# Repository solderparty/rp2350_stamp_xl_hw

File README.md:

# The RP2350 Stamp XL

The Stamp was created to allow you to use the **Raspberry Pi RP2350B** in your designs without having to solder small-pitch QFN chips or worry about lots of external circuitry.

The RP2350 Stamp XL is partially pad-compatible with the smaller Stamps. The left-side pads as well as half of the top and bottom ones are exactly the same.

All you need to get you started is a 5V supply or a LiPo battery. The Stamp will take care of the charging and switching the power sources.

The castellated edges with **2mm pitch** can be hand-soldered directly to a Carrier board, used with pin headers for more flexibility, or connected without soldering using [FlexyPins](https://docs.solder.party/flexypin), which are spring connectors designed for modules with castellated edges. You can find footprints for many PCB programs [here](https://github.com/solderparty/rp2xxx_stamp_footprints).

We were also able to squeeze in two new functional pads: an LDO EN pad, connected to the LDOs EN signal, and a BAT STAT, connected to the LiPo charger's STAT pin.

At only **1 by 1¾ inch**, the Stamp XL packs a lot of features:
* **16MB of FLASH**
* **500mA 3.3V LDO**
* **All 48 GPIOs broken out**
* **A footprint for a second QSPI FLASH/PSRAM**
* Footprints for SWD and UART JST connectors, pin-compatible with the Raspberry Pi Debug Probe
* LiPo supply and charging circuit (with charging LED)
* USB broken out
* SWD broken out
* Reset Button
* Bootsel Button
* 12MHz crystal

and of course, everything that comes with the Raspberry Pi RP2350 itself:
* Dual core ARM Cortex-M33 or Hazard3 @ 150MHz
* 520kB SRAM
* 2 UARTs
* 2 SPIs
* 2 I2Cs
* 24 PWM channels
* 12 PIO state machines
* 1 HSTX peripheral
* USB with Host and Device support

The RP2350 comes with a pre-programmed ROM UF2 Bootloader, by pulling the BOOTSEL pin low and resetting, or by double-pressing the RESET button (if the FW supports it), you can upload new firmware using the USB disk drive.

In addition to the Stamps we also offer a few reference designs, see the Carriers in the [Stamp-related category](https://docs.solder.party/rp2xxx-stamp-related) as well as our [Flux projects](https://docs.solder.party/flux).

The CircuitPython firmware for the Stamp comes with a built-in board files for the Carriers, for example you can access the RP2040 Stamp Carrier pins and interfaces by using `import stamp_carrier_board as board`. See [here](https://github.com/adafruit/circuitpython/tree/main/ports/raspberrypi/boards/solderparty_rp2040_stamp) for all the available Carrier board files.

# Links

For more information visit https://rp2350-stamp-xl.solder.party/

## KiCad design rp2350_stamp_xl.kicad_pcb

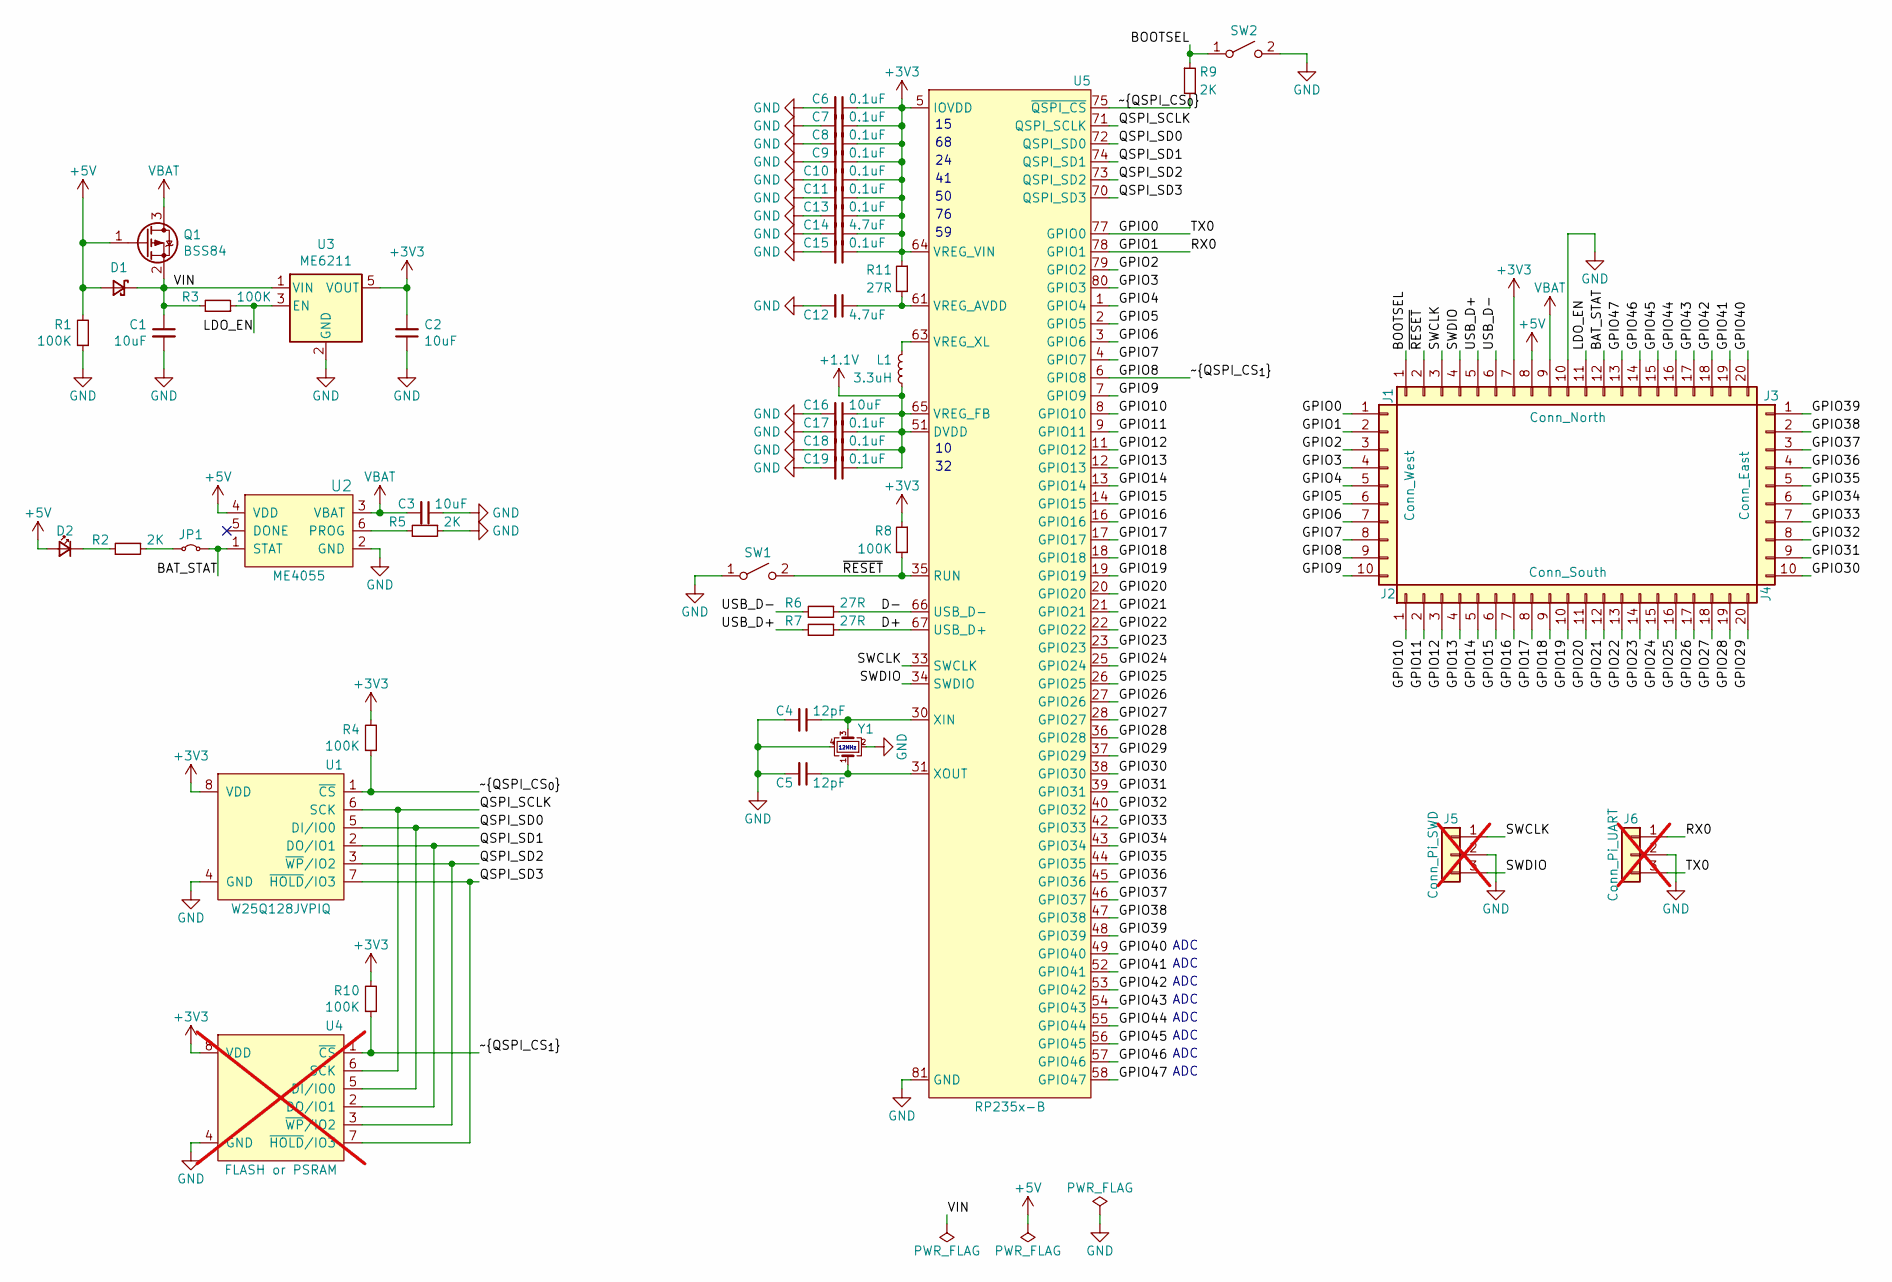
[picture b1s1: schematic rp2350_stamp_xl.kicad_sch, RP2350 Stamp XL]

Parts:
C1, C2, C3, C16: 10uF; C_0603_1608Metric
C4, C5: 12pF; C_0603_1608Metric
C6, C7, C8, C9, C10, C11, C13, C15, C17, C18, C19: 0.1uF; C_0603_1608Metric
C12, C14: 4.7uF; C_0603_1608Metric
D1: D_Schottky_Small; D_SOD-323; LCSC C114023
D2: LED_CHR; LED_0603_1608Metric
J1: Conn_North; Castellated_1x20_P2.00mm_Vertical
J2: Conn_West; Castellated_1x10_P2.00mm_Vertical
J3: Conn_East; Castellated_1x10_P2.00mm_Vertical
J4: Conn_South; Castellated_1x20_P2.00mm_Vertical
J5: Conn_Pi_SWD; JST_SH_BM03B-SRSS-TB_1x03-1MP_P1.00mm_Vertical; LCSC C7433439; not fitted
J6: Conn_Pi_UART; JST_SH_BM03B-SRSS-TB_1x03-1MP_P1.00mm_Vertical; LCSC C7433439; not fitted
JP1: SJ_STAT_LED; SolderJumper-2_P1.3mm_Bridged_RoundedPad1.0x1.5mm
L1: 3.3uH; L_Wuerth_MAPI-2512; LCSC C5832359
Q1: BSS84; SOT-23; LCSC C85202
R1, R3, R4, R8, R10: 100K; R_0603_1608Metric
R2, R5, R9: 2K; R_0603_1608Metric
R6, R7, R11: 27R; R_0603_1608Metric
SW1: SW_RESET; SW_SPST_B3U-1000P; LCSC C561514
SW2: SW_BOOTSEL; SW_SPST_B3U-1000P; LCSC C561514
U1: W25Q128JVPIQ; WSON-8-1EP_6x5mm_P1.27mm_EP3.4x4mm; LCSC C190862
U2: ME4055; SOT-23-6; LCSC C82121
U3: ME6211; SOT-23-5; LCSC C82942
U4: FLASH or PSRAM; SSOP-8_5.25x5.24mm_P1.27mm; not fitted
U5: RP235x-B; QFN-80_EP_10x10_Pitch0.4mm
Y1: CM4012M00012001; Crystal_SMD_2520-4Pin_2.5x2.0mm; LCSC C7294611

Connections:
+1.1V: C16.1, C17.1, C18.1, C19.1, L1.1, U5.10 (DVDD), U5.32 (DVDD), U5.51 (DVDD), U5.65 (VREG_FB)
+3V3: C2.2, C6.1, C7.1, C8.1, C9.1, C10.1, C11.1, C13.1, C14.1, C15.1, J1.7, R4.2, R8.1, R10.2, R11.1, U1.8 (VDD), U3.5 (VOUT), U4.8 (VDD), U5.5 (IOVDD), U5.15 (IOVDD), U5.24 (IOVDD), U5.29 (IOVDD), U5.41 (IOVDD), U5.50 (IOVDD), U5.59 (IOVDD), U5.60 (IOVDD), U5.64 (VREG_VIN), U5.68 (IOVDD), U5.69 (IOVDD), U5.76 (IOVDD)
+5V: D1.2 (A), D2.2 (A), J1.8, Q1.1 (G), R1.2, U2.4 (VDD)
/BAT_STAT: J1.12, JP1.2 (B), U2.1 (STAT)
/BOOTSEL: J1.1, R9.1, SW2.1 (A)
/D+: R7.1, U5.67 (USB_D+)
/D-: R6.1, U5.66 (USB_D-)
/GPIO0: J2.1, J6.3, U5.77 (GPIO0)
/GPIO1: J2.2, J6.1, U5.78 (GPIO1)
/GPIO2: J2.3, U5.79 (GPIO2)
/GPIO3: J2.4, U5.80 (GPIO3)
/GPIO4: J2.5, U5.1 (GPIO4)
/GPIO5: J2.6, U5.2 (GPIO5)
/GPIO6: J2.7, U5.3 (GPIO6)
/GPIO7: J2.8, U5.4 (GPIO7)
/GPIO8: J2.9, R10.1, U4.1 (~CS), U5.6 (GPIO8)
/GPIO9: J2.10, U5.7 (GPIO9)
/GPIO10: J4.1, U5.8 (GPIO10)
/GPIO11: J4.2, U5.9 (GPIO11)
/GPIO12: J4.3, U5.11 (GPIO12)
/GPIO13: J4.4, U5.12 (GPIO13)
/GPIO14: J4.5, U5.13 (GPIO14)
/GPIO15: J4.6, U5.14 (GPIO15)
/GPIO16: J4.7, U5.16 (GPIO16)
/GPIO17: J4.8, U5.17 (GPIO17)
/GPIO18: J4.9, U5.18 (GPIO18)
/GPIO19: J4.10, U5.19 (GPIO19)
/GPIO20: J4.11, U5.20 (GPIO20)
/GPIO21: J4.12, U5.21 (GPIO21)
/GPIO22: J4.13, U5.22 (GPIO22)
/GPIO23: J4.14, U5.23 (GPIO23)
/GPIO24: J4.15, U5.25 (GPIO24)
/GPIO25: J4.16, U5.26 (GPIO25)
/GPIO26: J4.17, U5.27 (GPIO26)
/GPIO27: J4.18, U5.28 (GPIO27)
/GPIO28: J4.19, U5.36 (GPIO28)
/GPIO29: J4.20, U5.37 (GPIO29)
/GPIO30: J3.10, U5.38 (GPIO30)
/GPIO31: J3.9, U5.39 (GPIO31)
/GPIO32: J3.8, U5.40 (GPIO32)
/GPIO33: J3.7, U5.42 (GPIO33)
/GPIO34: J3.6, U5.43 (GPIO34)
/GPIO35: J3.5, U5.44 (GPIO35)
/GPIO36: J3.4, U5.45 (GPIO36)
/GPIO37: J3.3, U5.46 (GPIO37)
/GPIO38: J3.2, U5.47 (GPIO38)
/GPIO39: J3.1, U5.48 (GPIO39)
/GPIO40: J1.20, U5.49 (GPIO40)
/GPIO41: J1.19, U5.52 (GPIO41)
/GPIO42: J1.18, U5.53 (GPIO42)
/GPIO43: J1.17, U5.54 (GPIO43)
/GPIO44: J1.16, U5.55 (GPIO44)
/GPIO45: J1.15, U5.56 (GPIO45)
/GPIO46: J1.14, U5.57 (GPIO46)
/GPIO47: J1.13, U5.58 (GPIO47)
/LDO_EN: J1.11, R3.1, U3.3 (EN)
/QSPI_SCLK: U1.6 (SCK), U4.6 (SCK), U5.71 (QSPI_SCLK)
/QSPI_SD0: U1.5 (DI/IO0), U4.5 (DI/IO0), U5.72 (QSPI_SD0)
/QSPI_SD1: U1.2 (DO/IO1), U4.2 (DO/IO1), U5.74 (QSPI_SD1)
/QSPI_SD2: U1.3 (~WP/IO2), U4.3 (~WP/IO2), U5.73 (QSPI_SD2)
/QSPI_SD3: U1.7 (~HOLD/IO3), U4.7 (~HOLD/IO3), U5.70 (QSPI_SD3)
/SWCLK: J1.3, J5.1, U5.33 (SWCLK)
/SWDIO: J1.4, J5.3, U5.34 (SWDIO)
/USB_D+: J1.5, R7.2
/USB_D-: J1.6, R6.2
/VIN: C1.1, D1.1 (K), Q1.2 (S), R3.2, U3.1 (VIN)
/~QSPI_CS_{0}: R4.1, R9.2, U1.1 (~CS), U5.75 (~QSPI_CS)
/~RESET: J1.2, R8.2, SW1.2 (B), U5.35 (RUN)
GND: C1.2, C2.1, C3.1, C4.2, C5.2, C6.2, C7.2, C8.2, C9.2, C10.2, C11.2, C12.2, C13.2, C14.2, C15.2, C16.2, C17.2, C18.2, C19.2, J1.10, J5.2, J6.2, R1.1, R5.1, SW1.1 (A), SW2.2 (B), U1.4 (GND), U1.9 (GND), U2.2 (GND), U3.2 (GND), U4.4 (GND), U4.9 (GND), U5.62 (GND), U5.81 (GND), Y1.2, Y1.4
unnamed: D2.1 (K), R2.2
unnamed: JP1.1 (A), R2.1
unnamed: R5.2, U2.6 (PROG)
unnamed: C12.1, R11.2, U5.61 (VREG_AVDD)
unnamed: L1.2, U5.63 (VREG_XL)
unnamed: C4.1, U5.30 (XIN), Y1.3
unnamed: C5.1, U5.31 (XOUT), Y1.1
VBAT: C3.2, J1.9, Q1.3 (D), U2.3 (VBAT)

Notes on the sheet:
ADC
12MHz

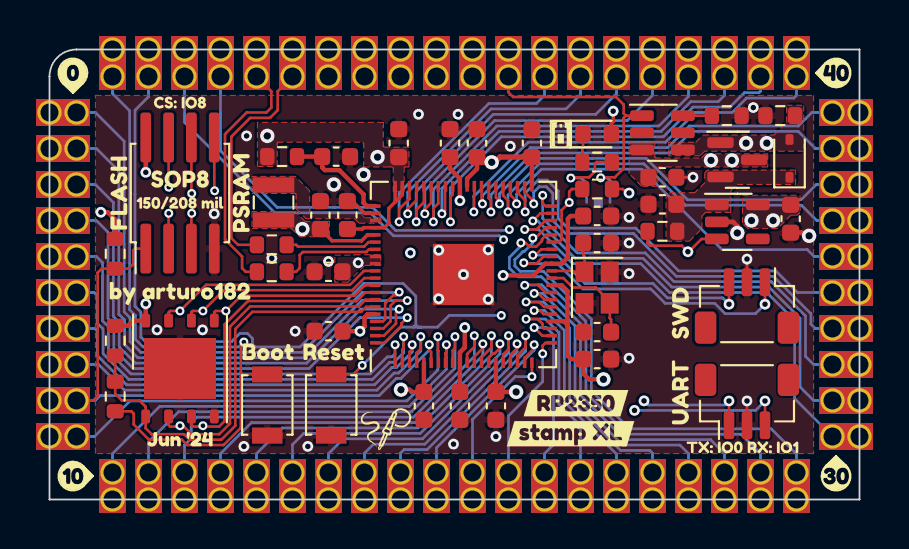
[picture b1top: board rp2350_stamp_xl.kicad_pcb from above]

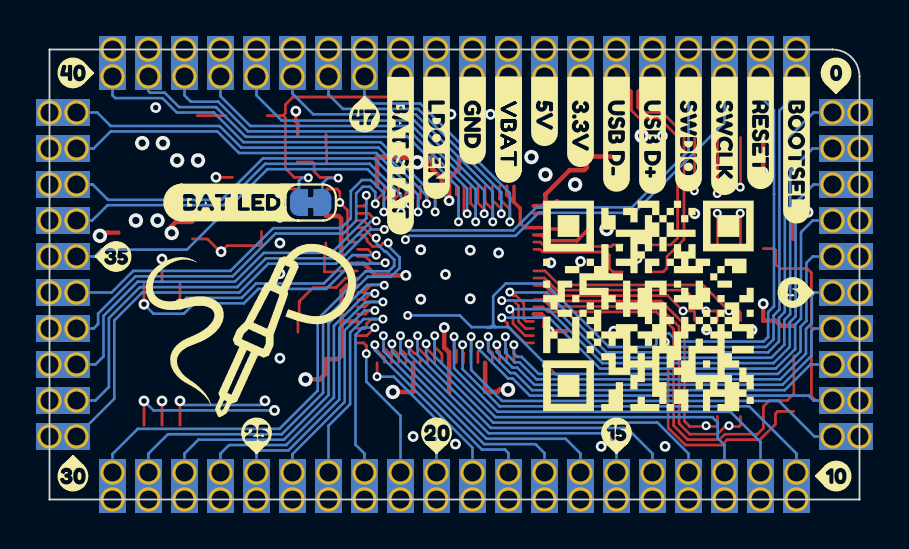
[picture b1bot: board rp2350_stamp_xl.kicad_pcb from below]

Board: 4 copper layers, 45.0 x 25.0 mm, 93 parts (26 on the bottom side), 77 nets.

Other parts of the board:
SP-LOGO: LOGO; SolderParty-New-Logo_3x2.5mm_SilkScreen
kibuzzard-65C6A7E6: G***; kibuzzard-65C6A7E6
kibuzzard-65C6A7EF: G***; kibuzzard-65C6A7EF
kibuzzard-65C6A855: G***; kibuzzard-65C6A855
kibuzzard-65C6A858: G***; kibuzzard-65C6A858
kibuzzard-65C59B9B: G***; kibuzzard-65C59B9B
kibuzzard-65C557A7: G***; kibuzzard-65C557A7
kibuzzard-65C55791: G***; kibuzzard-65C55791
kibuzzard-65CABD6A: G***; kibuzzard-65CABD6A
kibuzzard-65CABE96: G***; kibuzzard-65CABE96
kibuzzard-65CABECC: G***; kibuzzard-65CABECC
kibuzzard-653BD2BD: G***; kibuzzard-653BD2BD
kibuzzard-653BD2D7: G***; kibuzzard-653BD2D7
kibuzzard-653BD2FF: G***; kibuzzard-653BD2FF
kibuzzard-653BD3DA: G***; kibuzzard-653BD3DA
kibuzzard-653BD34E: G***; kibuzzard-653BD34E
kibuzzard-653BD35B: G***; kibuzzard-653BD35B
kibuzzard-653BD327: G***; kibuzzard-653BD327
kibuzzard-653BD339: G***; kibuzzard-653BD339
kibuzzard-653BD344: G***; kibuzzard-653BD344
kibuzzard-653BD355: G***; kibuzzard-653BD355
kibuzzard-653BD365: G***; kibuzzard-653BD365
kibuzzard-6577C6A3: G***; kibuzzard-6577C6A3
kibuzzard-6577C69C: G***; kibuzzard-6577C69C
kibuzzard-6578FE34: G***; kibuzzard-6578FE34
kibuzzard-6605B0A1: G***; kibuzzard-6605B0A1
kibuzzard-6605B0D5: G***; kibuzzard-6605B0D5
kibuzzard-6695ACF2, kibuzzard-6695ACF2#2: G***; kibuzzard-6695ACF2
kibuzzard-6695AD18, kibuzzard-6695AD18#2: G***; kibuzzard-6695AD18
kibuzzard-6695BC9C: G***; kibuzzard-6695BC9C
kibuzzard-6695BCB6: G***; kibuzzard-6695BCB6
kibuzzard-6695BF60, kibuzzard-6695BF60#2: G***; kibuzzard-6695BF60
kibuzzard-6695BFEA, kibuzzard-6695BFEA#2: G***; kibuzzard-6695BFEA
kibuzzard-6695C3C8: G***; kibuzzard-6695C3C8
kibuzzard-6695C4C9: G***; kibuzzard-6695C4C9
kibuzzard-6695C24F: G***; kibuzzard-6695C24F
kibuzzard-6695C28C: G***; kibuzzard-6695C28C
kibuzzard-6695C219: G***; kibuzzard-6695C219
kibuzzard-6695C372: G***; kibuzzard-6695C372
svg2mod: G***; svg2mod

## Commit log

2024-02-13 Rev 1
2024-07-16 Rev 3
    - Rev 2 added logo and QR Code
    - Put chip name on the board
    - Fixup pin markers to be uniform
    - Add battery icon
2024-07-29 Rev 3.5
    Fixup power stuff according to RPi's recommendations
2024-10-01 Fix BOM info, add README and LICENSE
